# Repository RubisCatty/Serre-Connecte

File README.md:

# Serre-Connecte
Projet final du programme de Génie Électrique par Sonia Michaud

Contient:
    Code source des trois modules: Maison, Serre et Capteur

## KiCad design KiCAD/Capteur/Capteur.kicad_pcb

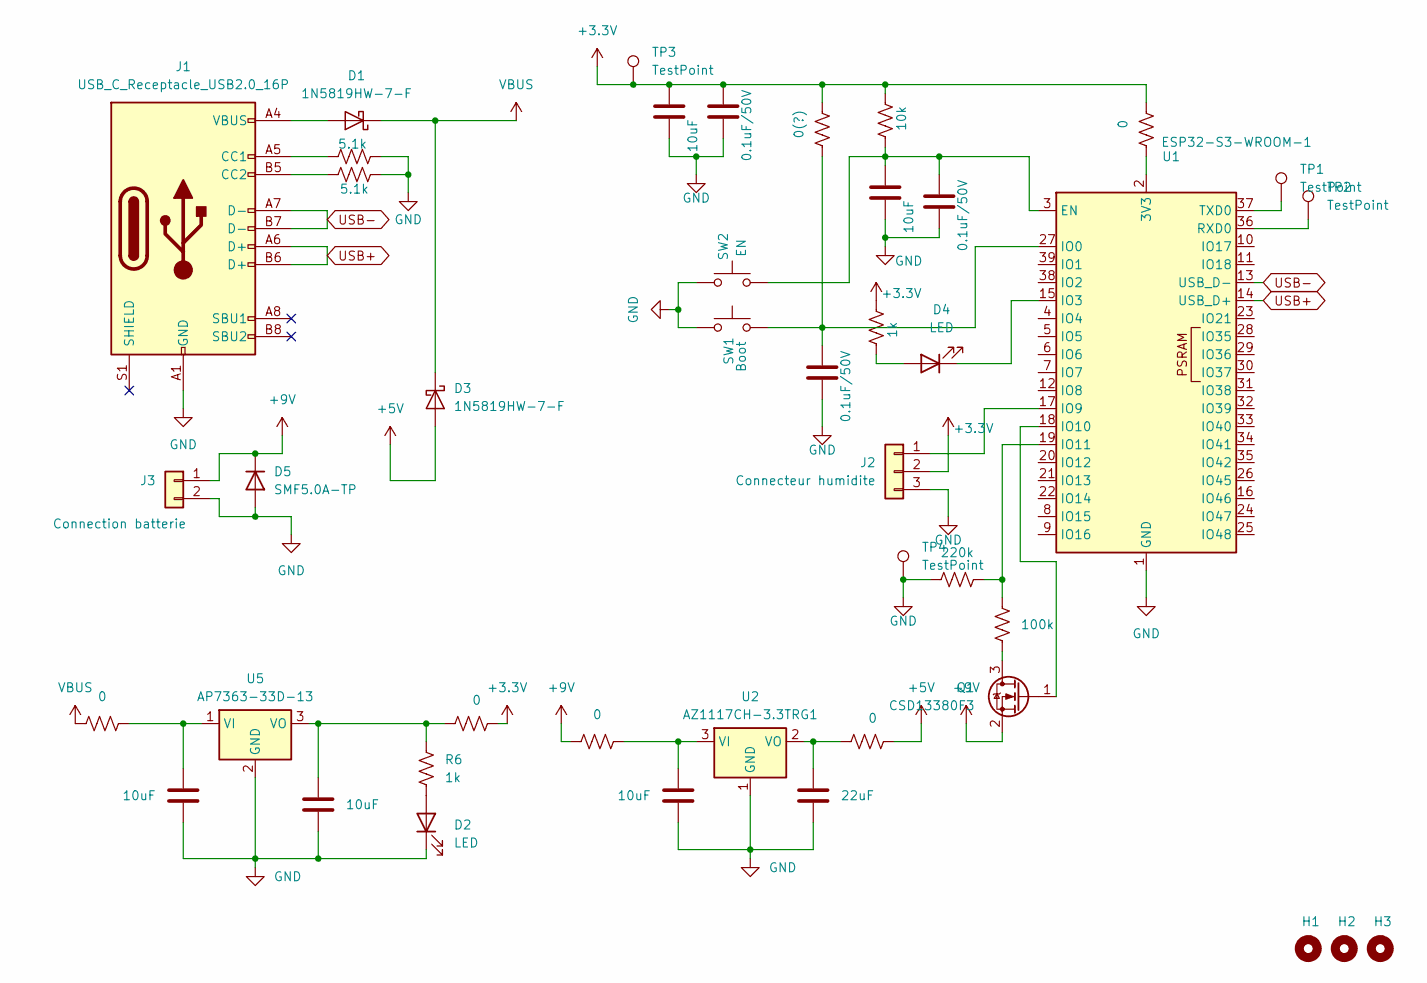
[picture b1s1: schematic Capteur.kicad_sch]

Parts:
C1, C3, C4: 0.1uF/50V; C_0805_2012Metric_Pad1.18x1.45mm_HandSolder; MPN CL21B104KCFWPNE
C2, C5, C6, C7, C8: 10uF; C_0805_2012Metric_Pad1.18x1.45mm_HandSolder; MPN CL21B106KOQNNNE
C9: 22uF; C_0805_2012Metric_Pad1.18x1.45mm_HandSolder; MPN CL21A226MQQNNNE
D1, D3: 1N5819HW-7-F; D_SOD-123; MPN 1N5819HW-7-F
D2, D4: LED; LED_0805_2012Metric_Pad1.15x1.40mm_HandSolder; MPN B1701NB--20D000114U1930
D5: SMF5.0A-TP; D_SOD-123F; MPN SMF5.0A-TP
H1, H2, H3: MountingHole; MountingHole_2.2mm_M2_ISO7380_Pad_TopOnly
J1: USB_C_Receptacle_USB2.0_16P; USB_C_Receptacle_GCT_USB4105-xx-A_16P_TopMnt_Horizontal; MPN UJ20-C-H-G-SMT-2A-P16-TR
J2: Connecteur humidite; PinHeader_1x03_P2.54mm_Vertical; MPN TSW-103-07-F-S
J3: Connection batterie; PinHeader_2x01_P2.54mm_Vertical; MPN 640456-2
Q1: CSD13380F3; SOT-23_Handsoldering; MPN SI3099-TP
R1, R4, R5, R11, R12: 0; R_0805_2012Metric_Pad1.20x1.40mm_HandSolder; MPN RC0805JR-070RL
R2, R3: 5.1k; R_0805_2012Metric_Pad1.20x1.40mm_HandSolder; MPN RK73H2ATTD5101F
R6, R8: 1k; R_0805_2012Metric_Pad1.20x1.40mm_HandSolder; MPN CRCW08051K00FKEA
R7: 0(?); R_0805_2012Metric_Pad1.20x1.40mm_HandSolder; MPN RC0805JR-070RL
R9: 10k; R_0805_2012Metric_Pad1.20x1.40mm_HandSolder; MPN CRCW080510K0FKEA
R10: 100k; R_0805_2012Metric_Pad1.20x1.40mm_HandSolder; MPN RC0805FR-07100KL
R13: 220k; R_0805_2012Metric_Pad1.20x1.40mm_HandSolder; MPN CRG0805F220K
SW1: Boot; SW_Tactile_SPST_NO_Straight_CK_PTS636Sx25SMTRLFS; MPN PTS636SM43SMTR LFS
SW2: EN; SW_Tactile_SPST_NO_Straight_CK_PTS636Sx25SMTRLFS; MPN PTS636SM43SMTR LFS
TP1, TP2, TP3, TP4: TestPoint; TestPoint_Pad_1.5x1.5mm
U1: ESP32-S3-WROOM-1; MPN ESP32-S3-WROOM-1-N8R8
U2: AZ1117CH-3.3TRG1; SOT-223-3_TabPin2; MPN AZ1117CH-3.3TRG1
U5: AP7363-33D-13; TO-252-2; MPN AP7363-33D-13

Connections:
+3.3V: C1.1, C8.1, J2.2, R4.2, R7.2, R8.1, R9.1, R11.2, TP3.1
+5V: D3.2 (A), R12.2
+9V: D5.1 (K), J3.1, Q1.2 (S), R1.1
GND: C1.2, C2.2, C3.2, C4.2, C5.2, C6.2, C7.2, C8.2, C9.2, D2.1 (K), D5.2 (A), J1.A1 (GND), J1.A12 (GND), J1.B1 (GND), J1.B12 (GND), J2.3, J3.2, R2.2, R3.2, R13.1, SW1.1, SW2.1, TP4.1, U1.1 (GND), U1.40 (GND), U1.41 (GND), U2.1 (GND), U5.2 (GND)
unnamed: D1.2 (A), J1.A4 (VBUS), J1.A9 (VBUS), J1.B4 (VBUS), J1.B9 (VBUS)
unnamed: D2.2 (A), R6.2
unnamed: D4.2 (A), R8.2
unnamed: D4.1 (K), U1.15 (IO3)
unnamed: J1.A5 (CC1), R3.1
unnamed: J1.B5 (CC2), R2.1
unnamed: J2.1, U1.17 (IO9)
unnamed: Q1.3 (D), R10.1
unnamed: Q1.1 (G), U1.18 (IO10)
unnamed: R4.1, U1.2 (3V3)
unnamed: C2.1, C3.1, R9.2, SW2.2, U1.3 (EN)
unnamed: C4.1, R7.1, SW1.2, U1.27 (IO0)
unnamed: R10.2, R13.2, U1.19 (IO11)
unnamed: TP2.1, U1.36 (RXD0)
unnamed: TP1.1, U1.37 (TXD0)
unnamed: C7.1, R1.2, U2.3 (VI)
unnamed: C9.1, R12.1, U2.2 (VO)
unnamed: C5.1, R5.2, U5.1 (VI)
unnamed: C6.1, R6.1, R11.1, U5.3 (VO)
USB+: J1.A6 (D+), J1.B6 (D+), U1.14 (USB_D+)
USB-: J1.A7 (D-), J1.B7 (D-), U1.13 (USB_D-)
VBUS: D1.1 (K), D3.1 (K), R5.1

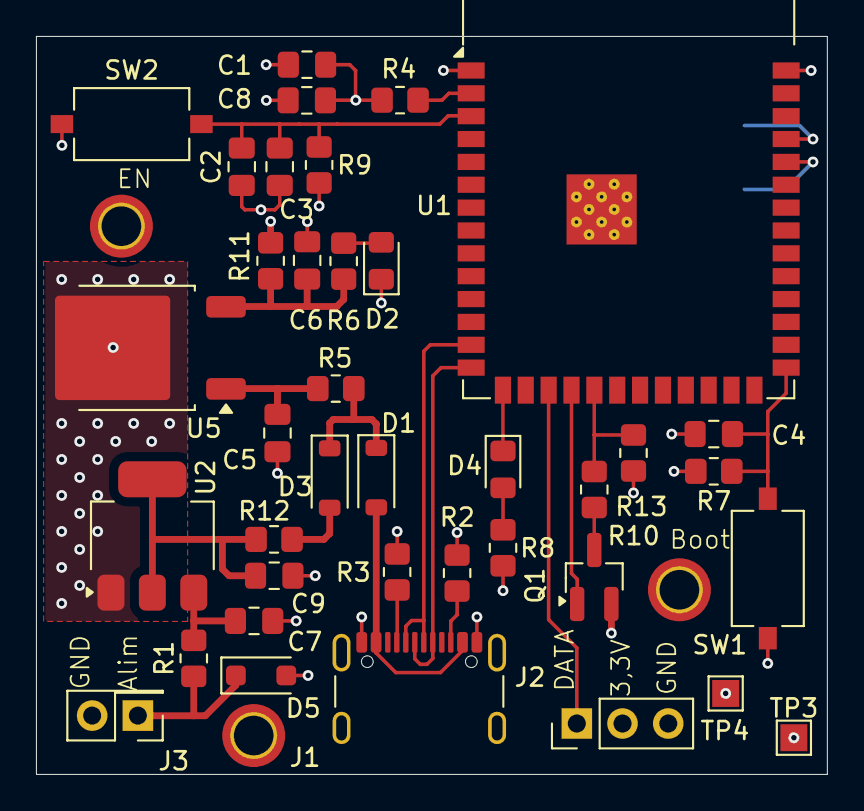
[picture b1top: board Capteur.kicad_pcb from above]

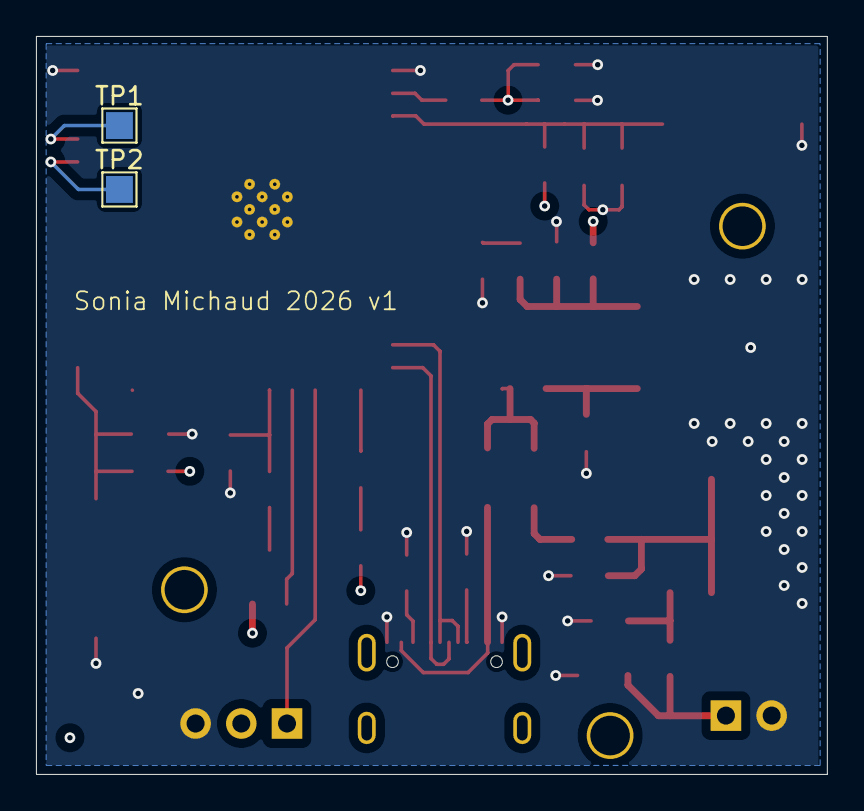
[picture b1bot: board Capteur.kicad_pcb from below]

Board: 4 copper layers, 43.9 x 41.0 mm, 43 parts (2 on the bottom side), 26 nets.

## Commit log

2026-05-22 première remise publique
2026-05-22 test 3D site
2026-05-22 ajout des modèle 3D
2026-05-24 ajout des projets KiCAD
